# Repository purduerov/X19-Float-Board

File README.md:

# X19 Float Board

The Float Board manages buoyancy systems, motor drivers, sensor telemetry, and power distribution for the Purdue ROV X19 vehicle.

---

## 🚀 Quickstart: Opening the Project (Recommended)

**Always open the project using the 1-click launcher:**

* **Windows:** Double-click `LAUNCH_KICAD.bat`
* **macOS / Linux:** Run `./LAUNCH_KICAD.sh`

### What the Launcher Does Automatically:
1. ⚙️ **Configures Git Hooks & Clean Filters:** Sets up Git to strip volatile viewport/zoom coordinates on every commit, preventing merge conflicts.
2. 🔄 **Auto-Updates Component Library:** Pulls the freshest symbols, footprints, and 3D models from `purdue-rov-kicad-lib` before opening.
3. 📐 **Opens KiCad:** Launches `X19-Float-Board.kicad_pro` with all 6 central library categories pre-linked.

---

## Cloning the Repository
Clone recursively to ensure the central component library is initialized:
```bash
git clone --recursive https://github.com/purduerov/X19-Float-Board.git
cd X19-Float-Board
```

## Central Component Library & Manager GUI

The project links to the central `purdue-rov-kicad-lib` submodule mapped across 6 categories in `sym-lib-table` and `fp-lib-table`:
- `rov_passives`: Resistors, capacitors, inductors, crystals
- `rov_power`: Voltage regulators, buck/boost converters, MOSFETs, diodes
- `rov_logic`: MCUs, logic ICs, op-amps, drivers, level shifters
- `rov_connectors`: Power terminals, XT60, headers, USB, JST connectors
- `rov_sensors`: IMUs, temperature, pressure sensors
- `rov_mech`: Mounting holes, standoffs, test points

### Launching the Library Manager GUI
To browse parts, inspect footprints, edit properties, or add/delete components in the shared library:
- **Windows:** Double-click `libs\purdue-rov-kicad-lib\LIBRARY_MANAGER.bat`
- **macOS / Linux:** Run `./libs/purdue-rov-kicad-lib/LIBRARY_MANAGER.sh`

## Schematic Hierarchy

The schematic is organized across functional sub-sheets:
- `X19-Float-Board.kicad_sch`: Root top-level sheet.
- `pwr.kicad_sch`: Power regulation and distribution.
- `stm32.kicad_sch`: Main microcontroller circuit and programming interface.
- `Motor.kicad_sch`: Motor driver stages and control signals.
- `sensor.kicad_sch`: Environmental and diagnostic sensor telemetry.
- `rf.kicad_sch`: Wireless/radio transceiver circuitry.
- `switch.kicad_sch`: Power switching logic.

## Design Rules & Clearances

- High-voltage / high-current motor traces maintain isolation rules configured in `custom_rules.kicad_dru`.
- All symbols must adhere to central library guidelines.

## Automated CI/CD & DevOps Preflight Checks

All CI/CD automation and tooling are centralized in [`purduerov/pcb-devops`](https://github.com/purduerov/pcb-devops):
1. **Automated Git Clean Filters:** Configured automatically by `.githooks/pre-commit` to prevent viewport/zoom merge noise.
2. **KiCad Symbol Linting:** Validates mandatory fields (`MPN`, `Manufacturer`, `Category`, `DigiKey`, `Datasheet`, `Temp_Range`) on all library components.
3. **ERC & DRC Validation:** Executes Electrical and Design Rules Checks via KiBot in GitHub Actions.
4. **Artifact Generation:** Automatically exports Schematic PDFs, Board Layout PDFs, and Interactive HTML BOMs on every pull request.

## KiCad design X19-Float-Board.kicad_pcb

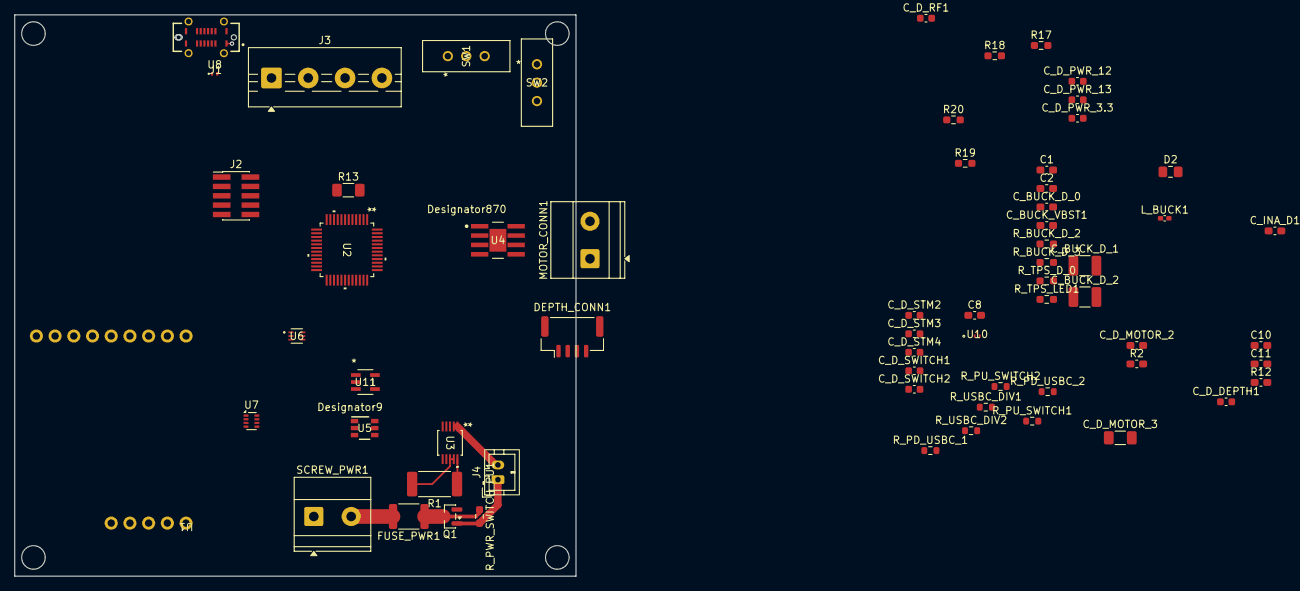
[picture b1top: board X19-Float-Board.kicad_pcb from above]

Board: 4 copper layers, 76.2 x 76.2 mm, 64 parts (0 on the bottom side), 44 nets.

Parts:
C1, C2: 1uF; C_0603_1608Metric_Pad1.08x0.95mm_HandSolder
C8, C10: 100nf; C_0603_1608Metric_Pad1.08x0.95mm_HandSolder
C11: 10nf; C_0603_1608Metric_Pad1.08x0.95mm_HandSolder
C_BUCK_D_0: .1uF; C_0603_1608Metric_Pad1.08x0.95mm_HandSolder
C_BUCK_D_1, C_BUCK_D_2: 22uF; C_1210_3225Metric_Pad1.33x2.70mm_HandSolder
C_BUCK_VBST1: 0.1 uF; C_0603_1608Metric_Pad1.08x0.95mm_HandSolder
C_D_DEPTH1: 100nF; C_0603_1608Metric
C_D_MOTOR_2: 10uf; C_0603_1608Metric_Pad1.08x0.95mm_HandSolder
C_D_MOTOR_3: 47uf; C_1206_3216Metric_Pad1.33x1.80mm_HandSolder
C_D_PWR_3.3, C_D_PWR_12, C_D_PWR_13: 4.7µF; C_0603_1608Metric
C_D_RF1: 100nF; C_0603_1608Metric
C_D_STM2, C_D_STM3: 100nF; C_0603_1608Metric
C_D_STM4: 2.2uF; C_0603_1608Metric
C_D_SWITCH1, C_D_SWITCH2: 100nF; C_0603_1608Metric
C_INA_D1: 100nf; C_0603_1608Metric_Pad1.08x0.95mm_HandSolder
D2: PWR Indicator; C_0805_2012Metric_Pad1.18x1.45mm_HandSolder
DEPTH_CONN1: 01x04; JST_GH_BM04B-GHS-TBT_1x04-1MP_P1.25mm_Vertical
FUSE_PWR1: 2A 12V PTC fuse; Fuse_1812_4532Metric
J1: USB4220-03-1040-C_REVA; GCT_USB4220-03-1040-C_REVA
J2: STLINK Connector; PinHeader_2x05_P1.27mm_Vertical_SMD
J3: SZ conn; TerminalBlock_MaiXu_MX126-5.0-04P_1x04_P5.00mm
J4: Conn_rotary_switch; JST_PH_B2B-PH-K_1x02_P2.00mm_Vertical
L_BUCK1: 3.3uH; C_0402_1005Metric_Pad0.74x0.62mm_HandSolder
MOTOR_CONN1: MOTOR_CONN2; TerminalBlock_Phoenix_MKDS-1,5-2-5.08_1x02_P5.08mm_Horizont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
Q1: DMP3099L; SOT-23
R1: 1 mΩ; R_2512_6332Metric_Pad1.40x3.35mm_HandSolder
R2, R12: 10k; C_0603_1608Metric_Pad1.08x0.95mm_HandSolder
R13: Generic Photoresistor; R_1206_3216Metric_Pad1.30x1.75mm_HandSolder
R17, R18, R19, R20: 10k; R_0603_1608Metric_Pad0.98x0.95mm_HandSolder
R_BUCK_D_2: 10k; R_0603_1608Metric_Pad0.98x0.95mm_HandSolder
R_BUCK_D_3: 33.2k; R_0603_1608Metric_Pad0.98x0.95mm_HandSolder
R_PD_USBC_1: 5.1k; R_0603_1608Metric
R_PD_USBC_2: 5.1kΩ; R_0603_1608Metric
R_PU_SWITCH1, R_PU_SWITCH2: 10kΩ; R_0603_1608Metric
R_PWR_SWITCH_PU1: 100k; R_0603_1608Metric_Pad0.98x0.95mm_HandSolder
R_TPS_D_0: 15k; R_0603_1608Metric_Pad0.98x0.95mm_HandSolder
R_TPS_LED1: 1k; R_0603_1608Metric_Pad0.98x0.95mm_HandSolder
R_USBC_DIV1: 20kΩ; R_0603_1608Metric
R_USBC_DIV2: 10kΩ; R_0603_1608Metric
SCREW_PWR1: 01x02; TerminalBlock_Phoenix_MKDS-1,5-2-5.08_1x02_P5.08mm_Horizont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
SW1, SW2: EG1218; EG_1218_EWI
U1: rf module
U2: STM32C542CCT6; LQFP48-7X7
U3: INA237AIDGSR; VSSOP_IDGSR_TEX
U4: DRV8231DDAR; DDA0008J-IPC_A
U5: TPS561208DDCR; DDC0006A_N
U6: TMP1075NDRLR; SOT5X3-6_DRL_TEX
U7: TPS2116DRL; SOT-583-8
U8: TPD1E05U06DPY; Texas_DPY0002A_0.6x1mm_P0.65mm
U10: ESD122DMXR; DMX3_TEX
U11: MIC5504-3.3YM5-TR; SOT-23-5_MC_MCH

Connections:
3.3 V: C8.1, C10.1, C11.1, C_D_DEPTH1.2, C_D_PWR_3.3.1, C_D_RF1.2, C_D_STM2.2, C_D_STM3.2, C_D_SWITCH1.2, C_D_SWITCH2.1, C_INA_D1.1, D2.2 (A), DEPTH_CONN1.1, R13.1, R17.2, R18.2, R19.2, R20.2, R_PU_SWITCH2.1, SW2.1, U1.6 (VIN), U2.9 (VREF+), U2.24 (VDD), U2.48 (VDD), U3.6 (VS), U4.4 (VREF), U6.5 (V+), U7.2 (VOUT), U7.7 (VOUT)
12 V: C_BUCK_D_0.1, C_BUCK_D_1.1, C_D_MOTOR_2.2, C_D_MOTOR_3.1, C_D_PWR_13.1, R1.2, U3.8 (VBUS), U3.9 (IN-), U4.5 (VM), U5.3 (VIN), U5.5 (EN)
/Motor/Motor PWM1: U2.30 (PA9), U4.3 (IN1)
/Motor/Motor PWM2: U2.29 (PA8), U2.40 (PB4), U4.2 (IN2)
/PWR/12 V High: C_D_PWR_12.1, Q1.2 (S), R1.1, U3.10 (IN+)
/Sensors/Depth SCL: DEPTH_CONN1.2, J3.1, R18.1, U2.42 (PB6), U3.5 (SCL), U6.1 (SCL)
/Sensors/Depth SDA: DEPTH_CONN1.3, J3.2, R17.1, U2.43 (PB7), U3.4 (SDA), U6.6 (SDA)
/Sensors/Light Voltage: R12.2, R13.2, U2.10 (PA0)
/TELEM/PWR ALERT: R20.1, U2.19 (PB1), U3.3 (ALERT)
/TELEM/TMP_ALERT: R19.1, U2.20 (PB2), U6.3 (ALERT)
/rf/RF INT: U1.9 (G0), U2.18 (PB0)
/rf/RF MISO: U1.11 (MISO), U2.16 (PA6)
/rf/RF MOSI: U1.12 (MOSI), U2.17 (PA7)
/rf/RF NSS: U1.13 (CS), U2.14 (PA4)
/rf/RF RST: U1.14 (RST), U2.13 (PA3)
/rf/RF SCK: U1.10 (SCK), U2.15 (PA5)
GND: C1.2, C2.2, C8.2, C10.2, C11.2, C_BUCK_D_0.2, C_BUCK_D_1.2, C_BUCK_D_2.2, C_D_DEPTH1.1, C_D_MOTOR_2.1, C_D_MOTOR_3.2, C_D_PWR_3.3.2, C_D_PWR_12.2, C_D_PWR_13.2, C_D_RF1.1, C_D_STM2.1, C_D_STM3.1, C_D_STM4.1, C_D_SWITCH1.1, C_D_SWITCH2.2, C_INA_D1.2, DEPTH_CONN1.4, J1.A1 (GND_A), J1.A12 (GND_A), J1.B1 (GND_B), J1.B12 (GND_A), J1.S1 (SHIELD), J1.S2 (SHIELD), J1.S3 (SHIELD), J1.S4 (SHIELD), J3.4, J4.2, R2.1, R12.1, R_BUCK_D_2.2, R_PD_USBC_1.2, R_PD_USBC_2.1, R_PU_SWITCH1.1, R_TPS_D_0.1, R_USBC_DIV1.1, SCREW_PWR1.1, SW1.1, U1.7 (GND), U2.8 (VREF-), U2.23 (VSS), U2.47 (VSS), U3.1 (A1), U3.2 (A0), U3.7 (GND), U4.7 (GND), U4.9 (Thermal_Pad), U5.1 (GND), U6.2 (GND), U6.4 (A0), U7.1 (GND), U8.1 (I/O), U10.1 (GND), U11.2 (GND)
unnamed: D2.1 (K), R_TPS_LED1.2
unnamed: J1.A5 (CC1), R_PD_USBC_2.2
unnamed: J1.B5 (CC2), R_PD_USBC_1.1
unnamed: J1.A7 (DN1), J1.B7 (DN2), U2.32 (PA11), U10.2 (IO1)
unnamed: J1.A6 (DP1), J1.B6 (DP2), U2.33 (PA12), U10.3 (IO2)
unnamed: J2.1, U2.34 (PA13)
unnamed: J2.2, U2.35 (VSS)
unnamed: J2.3, U2.36 (VDD)
unnamed: J2.4, U2.37 (PA14)
unnamed: J4.1, Q1.1 (G), R_PWR_SWITCH_PU1.2
unnamed: MOTOR_CONN1.1, U4.8 (OUT2)
unnamed: MOTOR_CONN1.2, U4.6 (OUT1)
unnamed: FUSE_PWR1.1, Q1.3 (D), R_PWR_SWITCH_PU1.1
unnamed: FUSE_PWR1.2, SCREW_PWR1.2
unnamed: R_PU_SWITCH2.2, SW1.3, U2.7 (NRST)
unnamed: R_USBC_DIV1.2, R_USBC_DIV2.2, U2.31 (PA10)
unnamed: R_PU_SWITCH1.2, SW2.3, U2.44 (PH2-BOOT0)
unnamed: C_D_STM4.2, U2.22 (VCAP)
unnamed: R2.2, U4.1 (IPROPI)
unnamed: C_BUCK_VBST1.2, L_BUCK1.1, U5.2 (SW)
unnamed: C_BUCK_VBST1.1, U5.6 (VBST)
unnamed: R_BUCK_D_2.1, R_BUCK_D_3.1, U5.4 (VFB)
unnamed: C_BUCK_D_2.1, L_BUCK1.2, R_BUCK_D_3.2, U7.3 (VIN1), U7.5 (MODE)
unnamed: R_TPS_D_0.2, U7.4 (PR1)
unnamed: R_TPS_LED1.1, U7.8 (ST)
unnamed: C2.1, U7.6 (VIN2), U11.5 (VOUT)
VBUS_A: C1.1, J1.A4 (VBUS_A), J1.A9 (VBUS_A), J1.B4 (VBUS_B), J1.B9 (VBUS_B), J3.3, R_USBC_DIV2.1, U8.2 (GND), U11.1 (VIN), U11.3 (EN)

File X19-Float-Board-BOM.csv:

Row,Description,Part,References,Value,Footprint,Quantity Per PCB,Status,Datasheet,Manufacturer,MPN,DigiKey,Temp_Range,Category,Verified,MF,Package,Price,Check_prices,STANDARD,PARTREV,SnapEDA_Link,MP,Purchase-URL,Availability,SNAPEDA_PN,Sim.Pins
1,"Unpolarized capacitor, small symbol",C_Small,C11,10nf,C_0603_1608Metric_Pad1.08x0.95mm_HandSolder,1, ,,,,,,,,,,,,,,,,,,,
2,"Unpolarized capacitor, small symbol",C_Small,C8 C10 C_INA_D1,100nf,C_0603_1608Metric_Pad1.08x0.95mm_HandSolder,3, ,,,,,,,,,,,,,,,,,,,
3,"Unpolarized capacitor, small symbol",C_Small,C1 C2,1uF,C_0603_1608Metric_Pad1.08x0.95mm_HandSolder,2, ,,,,,,,,,,,,,,,,,,,
4,"Unpolarized capacitor, small symbol",C_Small,C_BUCK_D_0,.1uF,C_0603_1608Metric_Pad1.08x0.95mm_HandSolder,1, ,,,,,,,,,,,,,,,,,,,
5,"Unpolarized capacitor, small symbol",C_Small,C_BUCK_D_1 C_BUCK_D_2,22uF,C_1210_3225Metric_Pad1.33x2.70mm_HandSolder,2, ,,,,,,,,,,,,,,,,,,,
6,"Unpolarized capacitor, small symbol",C_Small,C_BUCK_VBST1,0.1 uF,C_0603_1608Metric_Pad1.08x0.95mm_HandSolder,1, ,,,,,,,,,,,,,,,,,,,
7,"Unpolarized capacitor, small symbol",C_Small,C_D_DEPTH1 C_D_RF1 C_D_STM2 C_D_STM3 C_D_SWITCH1 C_D_SWITCH2,100nF,C_0603_1608Metric,6, ,,,,,,,,,,,,,,,,,,,
8,Unpolarized capacitor,C,C_D_MOTOR_2,10uf,C_0603_1608Metric_Pad1.08x0.95mm_HandSolder,1, ,,,,,,,,,,,,,,,,,,,
9,Unpolarized capacitor,C,C_D_MOTOR_3,47uf,C_1206_3216Metric_Pad1.33x1.80mm_HandSolder,1, ,,,,,,,,,,,,,,,,,,,
10,"Unpolarized capacitor, small symbol",C_Small,C_D_PWR_3.3 C_D_PWR_12 C_D_PWR_13,4.7µF,C_0603_1608Metric,3, ,,,,,,,,,,,,,,,,,,,
11,"Unpolarized capacitor, small symbol",C_Small,C_D_STM4,2.2uF,C_0603_1608Metric,1, ,,,,,,,,,,,,,,,,,,,
12,Light emitting diode,LED,D2,PWR Indicator,C_0805_2012Metric_Pad1.18x1.45mm_HandSolder,1, ,,,,,,,,,,,,,,,,,,,1=K 2=A
13,"Generic connector, single row, 01x04, script generated",Conn_01x04_Pin,DEPTH_CONN1 J2 J3,01x04,JST_GH_BM04B-GHS-TBT_1x04-1MP_P1.25mm_Vertical,3, ,,,,,,,,,,,,,,,,,,,
14,Fuse,Fuse,FUSE_PWR1,2A 12V PTC fuse,Fuse_1812_4532Metric,1, ,,,,,,,,,,,,,,,,,,,
15,Type C USB 2.0 Connector,USB4220-03-1040-C_REVA,J1,USB4220-03-1040-C_REVA,GCT_USB4220-03-1040-C_REVA,1, ,,Global Connector Technology,,,,,,Global Connector Technology,None,None,https://www.snapeda.com/parts/USB4220-03-0880-C/Global+Conne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,Manufacturer Recommendations,A,https://www.snapeda.com/parts/USB4220-03-0880-C/Global+Conne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,USB4220-03-0880-C,https://www.snapeda.com/api/url_track_click_mouser/?unipart_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 Connector Technology&part_name=USB4220-03-0880-C&search_term=usb4220-03-0880-c,In Stock,USB4220-03-0880-C,
16,"Inductor, small symbol",L_Small,L_BUCK1,3.3uH,,1, ,,,,,,,,,,,,,,,,,,,
17,"Generic connector, single row, 01x02, script generated",Conn_01x02_Pin,MOTOR_CONN1,MOTOR_CONN2,"TerminalBlock_Phoenix_MKDS-1,5-2-5.08_1x02_P5.08mm_Horizontal",1, ,,,,,,,,,,,,,,,,,,,
18,"Resistor, US symbol",R_US,R1,1 mΩ,R_2512_6332Metric_Pad1.40x3.35mm_HandSolder,1, ,,,,,,,,,,,,,,,,,,,
19,"Resistor, small US symbol",R_Small_US,R12 R17 R18 R19 R20 R_BUCK_D_2,10k,,6, ,,,,,,,,,,,,,,,,,,,
20,"Resistor, US symbol",R_US,R2,10k,,1, ,,,,,,,,,,,,,,,,,,,
21,Photoresistor,R_Photo,R13,Generic Photoresistor,,1, ,,,,,,,,,,,,,,,,,,,
22,"Resistor, small US symbol",R_Small_US,R_BUCK_D_3,33.2k,,1, ,,,,,,,,,,,,,,,,,,,
23,"Resistor, small US symbol",R_Small_US,R_PD_USBC_1,5.1k,R_0603_1608Metric,1, ,,,,,,,,,,,,,,,,,,,
24,"Resistor, small US symbol",R_Small_US,R_PD_USBC_2,5.1kΩ,R_0603_1608Metric,1, ,,,,,,,,,,,,,,,,,,,
25,"Resistor, small US symbol",R_Small_US,R_PU_SWITCH1 R_PU_SWITCH2 R_USBC_DIV2,10kΩ,R_0603_1608Metric,3, ,,,,,,,,,,,,,,,,,,,
26,"Resistor, small US symbol",R_Small_US,R_TPS_D_0,15k,,1, ,,,,,,,,,,,,,,,,,,,
27,"Resistor, small US symbol",R_Small_US,R_TPS_LED1,1k,,1, ,,,,,,,,,,,,,,,,,,,
28,"Resistor, small US symbol",R_Small_US,R_USBC_DIV1,20kΩ,R_0603_1608Metric,1, ,,,,,,,,,,,,,,,,,,,
29,"Generic screw terminal, single row, 01x02, script generated (kicad-library-utils/schlib/autogen/connector/)",Screw_Terminal_01x02,SCREW_PWR1,01x02,"TerminalBlock_Phoenix_MKDS-1,5-2-5.08_1x02_P5.08mm_Horizontal",1, ,,,,,,,,,,,,,,,,,,,
30,,EG1218,SW1 SW2,EG1218,EG_1218_EWI,2, ,EG1218,,,,,,,,,,,,,,,,,,
31,,rfm95adafruitmodule,U1,,rf module,1, ,,,,,,,,,,,,,,,,,,,
32,,DRV8231DDAR,U4,DRV8231DDAR,DDA0008J-IPC_A,1, ,https://www.ti.com/lit/gpn/drv8231,,,,,,,,,,,,,,,,,,
33,,ESD122DMXR,U10,ESD122DMXR,DMX3_TEX,1, ,https://www.ti.com/lit/gpn/esd122,,,,,,,,,,,,,,,,,,
34,"85V, 16-Bit, High-Precision Current/Voltage/Power Monitor with I2C",INA237AIDGSR,U3,INA237AIDGSR,VSSOP_IDGSR_TEX,1, ,https://www.ti.com/lit/ds/symlink/ina237.pdf,Texas Instruments,INA237AIDGSR,296-INA237AIDGSRCT-ND,-40°C to 125°C,Sensors,Yes,,,,,,,,,,,,
35,300mA Single LDO Regulator 3.3V Output SOT-23-5,MIC5504-3.3YM5-TR,U11,MIC5504-3.3YM5-TR,SOT-23-5_MC_MCH,1, ,https://ww1.microchip.com/downloads/en/DeviceDoc/MIC550X-300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,Microchip Technology,MIC5504-3.3YM5-TR,576-4763-1-ND,-40°C to 125°C,Power,Yes,,,,,,,,,,,,
36,"ARM Cortex-M33 32-bit MCU+FPU, 144MHz, 256KB Flash, 64KB RAM, LQFP-48",STM32C542CCT6,U2,STM32C542CCT6,LQFP48-7X7,1, ,https://www.st.com/resource/en/datasheet/stm32c542cc.pdf,STMicroelectronics,STM32C542CCT6,https://www.digikey.com/en/products/detail/stmicroelectronic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,-40°C to 125°C,Logic,,,,,,,,,,,,,
37,,TMP1075NDRLR,U6,TMP1075NDRLR,SOT5X3-6_DRL_TEX,1, ,https://www.ti.com/lit/gpn/tmp1075,,,,,,,,,,,,,,,,,,
38,"1-Channel ESD Protection for Super-Speed USB 3.0 Interface, X1SON-2",TPD1E05U06DPY,U8,TPD1E05U06DPY,Texas_DPY0002A_0.6x1mm_P0.65mm,1, ,https://www.ti.com/lit/ds/symlink/tpd1e05u06.pdf,,,,,,,,,,,,,,,,,,
39,"2 Channnels Power Mux with Manual and Priority Switchover, 1.6-5.5V Input Voltage, 2.5A Output Current, Ron 40 mOhm, SOT-583-8",TPS2116DRL,U7,TPS2116DRL,SOT-583-8,1, ,https://www.ti.com/lit/ds/symlink/tps2116.pdf,,,,,,,,,,,,,,,,,,
40,,TPS561208DDCR,U5,TPS561208DDCR,DDC0006A_N,1, ,https://www.ti.com/lit/gpn/tps561208,,,,,,,,,,,,,,,,,,





Project info:
Schematic:,X19-Float-Board
Variant:,default
Revision:,
Date:,2026-10-24_18-00-48
KiCad Version:,10.0.5-unknown-202607221313~667fa36054~ubuntu25.10.1
Statistics:
Component Groups:,40
Component Count:,61
Fitted Components:,61
Number of PCBs:,1
Total Components:,61

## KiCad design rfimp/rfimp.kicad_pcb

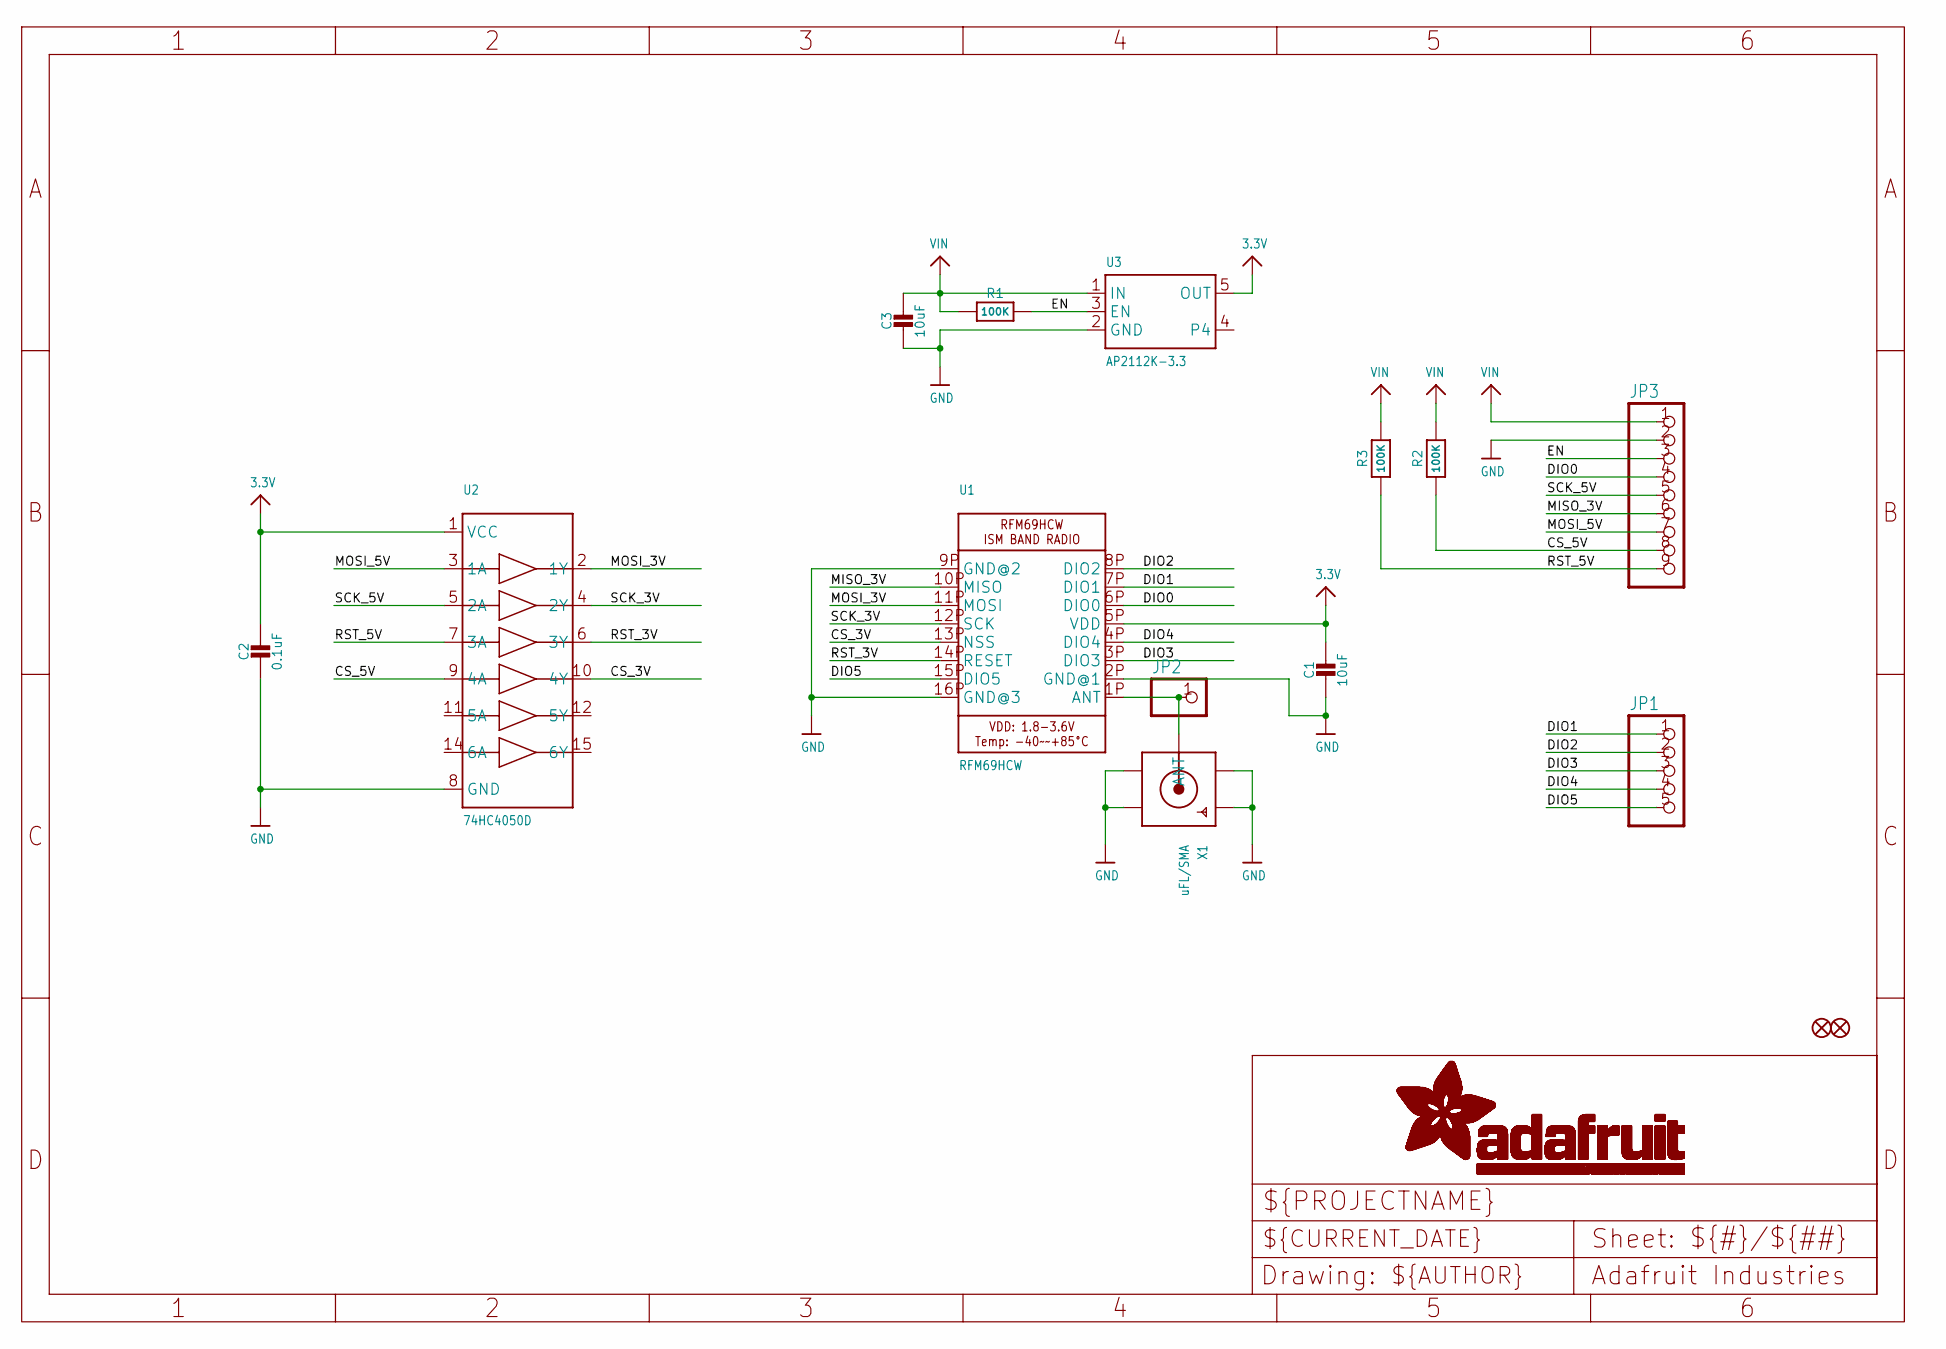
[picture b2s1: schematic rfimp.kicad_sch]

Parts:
C1, C3: 10uF; 0805-NO
C2: 0.1uF; 0805-NO
FID1, FID2: FIDUCIAL""; FIDUCIAL_1MM
JP1: HEADER-1X570MIL; 1X05_ROUND_70
JP2: HEADER-1X1ROUND; 1X01_ROUND
JP3: HEADER-1X970MIL; 1X09_ROUND_70
R1, R2, R3: 100K; 0805-NO
U1: RFM69HCW; RFMHCW_SMT
U2: 74HC4050D; TSSOP16
U3: AP2112K-3.3; SOT23-5
X1: uFL/SMA; SMA_EDGELAUNCH_UFL

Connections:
3.3V: C1.1, C2.1, U1.5P (VDD), U2.1 (VCC), U3.5 (OUT)
CS_3V: U1.13P (NSS), U2.10 (4Y)
CS_5V: JP3.8, R2.1, U2.9 (4A)
DIO0: JP3.4, U1.6P (DIO0)
DIO1: JP1.1, U1.7P (DIO1)
DIO2: JP1.2, U1.8P (DIO2)
DIO3: JP1.3, U1.3P (DIO3)
DIO4: JP1.4, U1.4P (DIO4)
DIO5: JP1.5, U1.15P (DIO5)
EN: JP3.3, R1.2, U3.3 (EN)
GND: C1.2, C2.2, C3.2, JP3.2, U1.2P (GND@1), U1.9P (GND@2), U1.16P (GND@3), U2.8 (GND), U3.2 (GND), X1.GND@1 (GND1), X1.GND@2 (GND2), X1.GND@3 (GND3), X1.GND@4 (GND4)
MISO_3V: JP3.6, U1.10P (MISO)
MOSI_3V: U1.11P (MOSI), U2.2 (1Y)
MOSI_5V: JP3.7, U2.3 (1A)
unnamed: JP2.1, U1.1P (ANT), X1.P (ANT)
RST_3V: U1.14P (RESET), U2.6 (3Y)
RST_5V: JP3.9, R3.1, U2.7 (3A)
SCK_3V: U1.12P (SCK), U2.4 (2Y)
SCK_5V: JP3.5, U2.5 (2A)
VIN: C3.1, JP3.1, R1.1, R2.2, R3.2, U3.1 (IN)

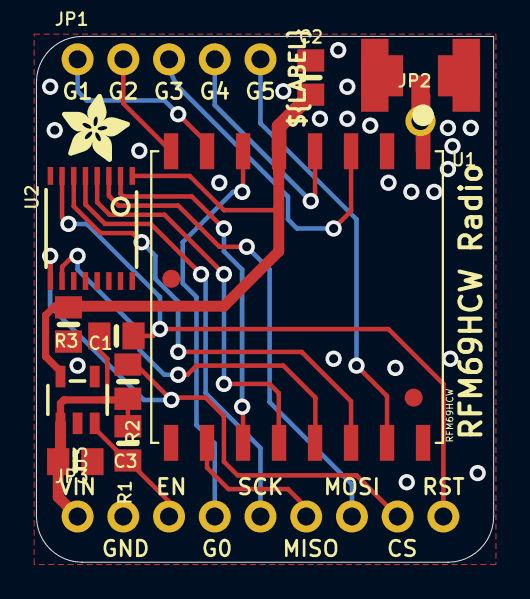
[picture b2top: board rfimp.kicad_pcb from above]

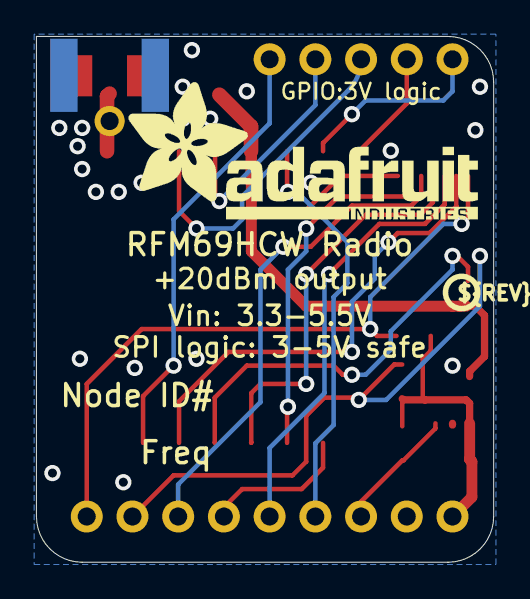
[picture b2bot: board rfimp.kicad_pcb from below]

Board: 2 copper layers, 25.4 x 29.2 mm, 18 parts (2 on the bottom side), 20 nets.

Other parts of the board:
U$8: ADAFRUIT_3.5MM
U$14: PCBFEAT-REV-040
U$19: ADAFRUIT_TEXT_20MM
